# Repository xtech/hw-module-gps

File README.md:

# hw-module-gps — OpenMower GPS Module

A KiCad PCB design for a GPS module intended for the OpenMower universal mainboard. Part of the [OpenMower project](https://github.com/clemensElflein/openmower) — open-source RTK GPS lawn mowing robotics.

---

## Board Preview

| Top | Bottom |
|-----|--------|
|  |  |

3D render:

---

## Repository Structure

```
.
├── hw-module-gps.kicad_sch   # Schematic
├── hw-module-gps.kicad_pcb   # PCB layout
├── hw-module-gps.kicad_pro   # KiCad project
├── .kibot.yaml               # KiBot automation config
├── release/                  # Generated production files
│   ├── hw-module-gps-JLCPCB.zip       # Gerbers for JLCPCB
│   ├── hw-module-gps_bom_jlc.csv      # BOM (JLCPCB format)
│   ├── hw-module-gps_cpl_jlc.csv      # Pick-and-place (JLCPCB format)
│   ├── hw-module-gps-schematic.pdf    # Schematic PDF
│   └── hw-module-gps-ibom.html        # Interactive BOM
├── 3d/                       # Custom 3D models
├── xcore-lib/                # Custom symbol library
└── logos/                    # SVG assets used on PCB silkscreen
```

---

## Ordering from JLCPCB

All production files are pre-generated in `release/`:

1. Upload `release/hw-module-gps-JLCPCB.zip` as gerbers
2. Enable **PCB Assembly**, upload:
   - `release/hw-module-gps_bom_jlc.csv` as BOM
   - `release/hw-module-gps_cpl_jlc.csv` as CPL
3. Use `release/hw-module-gps-ibom.html` (open in browser) to verify component placement

---

## Regenerating Release Files

Requires Docker.

```bash
./run-kibot-docker.sh
```

This runs [KiBot](https://github.com/INTI-CMNB/KiBot) via `ghcr.io/inti-cmnb/kicad9_auto:1.8.5` and regenerates all files in `release/`.

---

## Opening the Design

Requires [KiCad 9](https://www.kicad.org/). Open `hw-module-gps.kicad_pro`.

---

## Legal

Before building a robot using these designs, verify that doing so is permitted in your jurisdiction. Patents and local regulations may apply.

The files are distributed **without any warranty** — no guarantee of safety, legality, or correct function. You need the technical knowledge to evaluate and use this design. The author is not liable for any damages.

## License

<br />
Licensed under <a rel="license" href="https://creativecommons.org/licenses/by/4.0/">Creative Commons Attribution 4.0 International</a>.

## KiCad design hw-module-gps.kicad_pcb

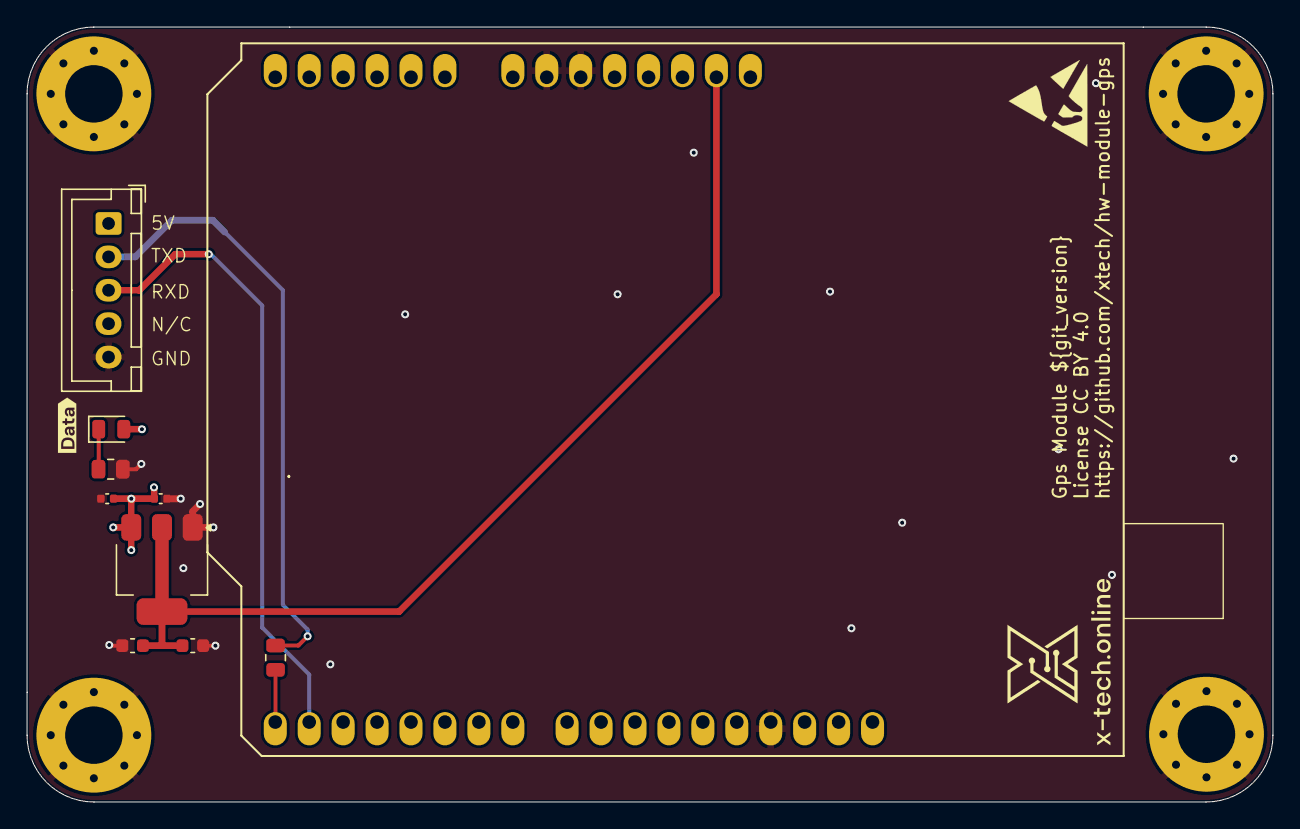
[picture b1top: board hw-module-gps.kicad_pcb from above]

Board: 4 copper layers, 93.2 x 58.0 mm, 22 parts (1 on the bottom side), 7 nets.

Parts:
C37: 10uF; C_0402_1005Metric
C63: 100nF; C_0402_1005Metric
C119, C120: 22uF; C_0603_1608Metric
D25: LED GREEN; LED_0805_2012Metric
H5, H6, H10, H15: MountingHole_Pad; MountingHole_4.3mm_M4_Pad_Via
J29: Conn_01x05; JST_XH_B5B-XH-A_1x05_P2.50mm_Vertical
LOGO2: ESD-Logo_6.6x6mm_SilkScreen
R44: 1k; R_0805_2012Metric
R59: 2.2k; R_0805_2012Metric
U12: AMS1117-3.3; SOT-223-3_TabPin2
U42: 2.54mm 1x6 socket; Dummy
U43, U44: 2.54mm 1x8 socket; Dummy
U45: 2.54mm 1x10 socket; Dummy
XA1: Ardusimple_F9P; Arduino_Uno_Shield_Ardusimple_Budget
kibuzzard-69B58D65, kibuzzard-69B58D65#2: G***; kibuzzard-69B58D65
kibuzzard-67111AE1: G***; kibuzzard-67111AE1

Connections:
/3.3V: C119.2, C120.2, U12.2 (VO), XA1.IORF (IOREF)
/5V: C37.2, C63.2, D25.2 (A), J29.1, U12.3 (VI), XA1.5V1 (5V)
/RXD: J29.3, XA1.D1 (RXD)
/TXD: J29.2, R59.2
GND: C37.1, C63.1, C119.1, C120.1, H5.1, H6.1, H10.1, H15.1, J29.5, R44.2, U12.1 (GND), XA1.GND1 (GND), XA1.GND2 (GND), XA1.GND3 (GND)
unnamed: D25.1 (K), R44.1
unnamed: R59.1, XA1.D0 (TXD)

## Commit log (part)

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2026-06-05 Initial Release
2026-06-05 deploy: 38561f2054f8922d19caf9dfa5b80f20f56d1050
2026-06-05 updated CPL
2026-06-05 deploy: 6ceeae576286d7685849d460f062035b10ff896a

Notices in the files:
hw-module-gps.kicad_pcb:
License CC BY 4.0
